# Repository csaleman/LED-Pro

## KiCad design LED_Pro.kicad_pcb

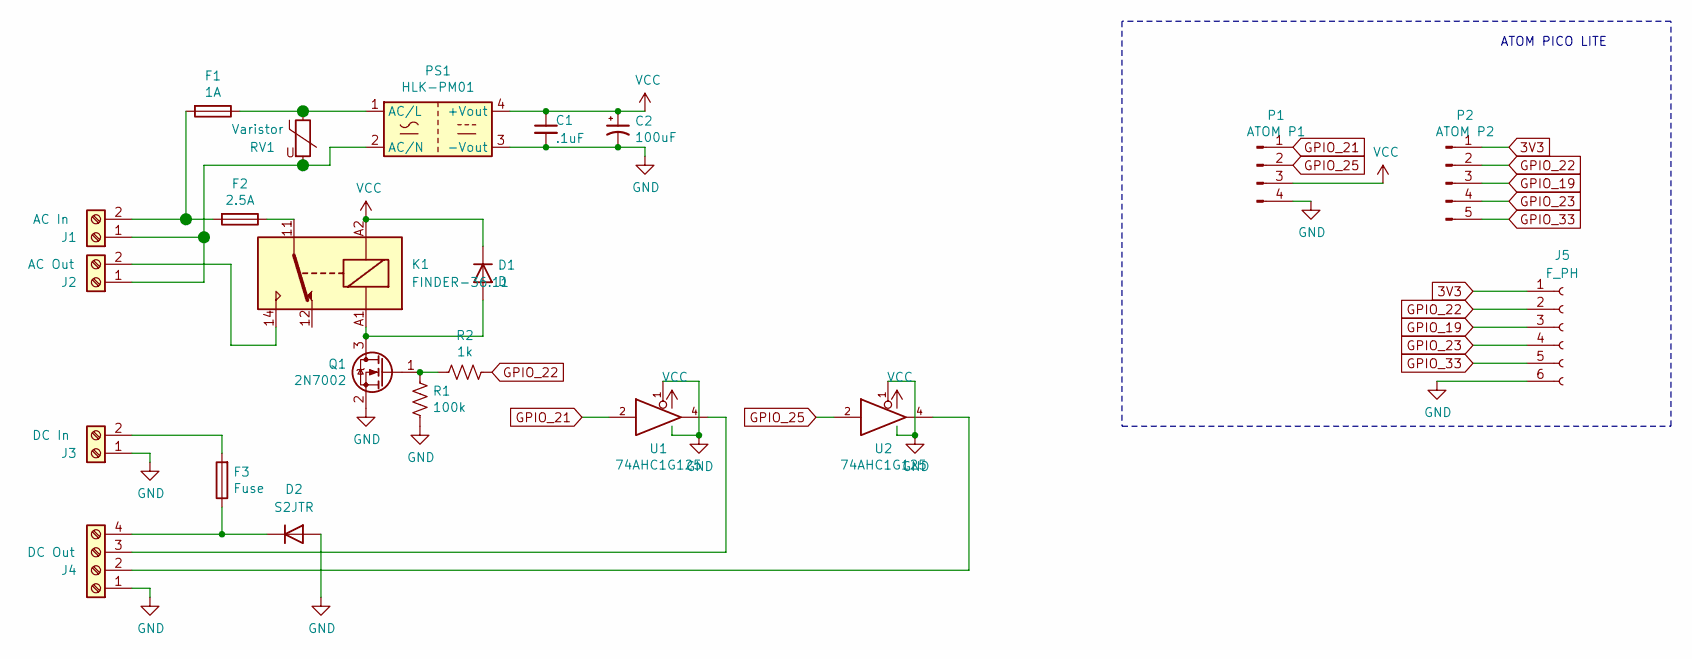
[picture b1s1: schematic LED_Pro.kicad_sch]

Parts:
C1: .1uF; C_0805_2012Metric
C2: 100uF; C_1206_3216Metric
D1: D; D_0805_2012Metric
D2: S2JTR; D_SMB
F1: 1A; RST 1-BULK
F2: 2.5A; RST 1-BULK
F3: Fuse; Fuseholder_Blade_Mini_Keystone_3568
J1: AC In; TerminalBlock_Phoenix_PT-1,5-2-5.0-H_1x02_P5.00mm_Horizontal
J2: AC Out; TerminalBlock_Phoenix_PT-1,5-2-5.0-H_1x02_P5.00mm_Horizontal
J3: DC In; TerminalBlock_Phoenix_PT-1,5-2-5.0-H_1x02_P5.00mm_Horizontal
J4: DC Out; TerminalBlock_Phoenix_PT-1,5-4-5.0-H_1x04_P5.00mm_Horizontal
J5: F_PH; PinSocket_1x06_P2.54mm_Vertical
K1: FINDER-36.11; Relay_SPDT_Finder_36.11
P1: ATOM P1; PinHeader_1x04_P2.54mm_Vertical
P2: ATOM P2; PinHeader_1x05_P2.54mm_Vertical
PS1: HLK-PM01; Converter_ACDC_HiLink_HLK-PMxx
Q1: 2N7002; SOT-23
R1: 100k; R_0805_2012Metric
R2: 1k; R_0805_2012Metric
RV1: Varistor; RV_Disc_D9mm_W3.4mm_P5mm
U1, U2: 74AHC1G125; SOT-23-5

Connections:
3V3: J5.1, P2.1
GND: C1.2, C2.2, D2.2 (A), J3.1, J4.1, J5.6, P1.4, PS1.3 (-Vout), Q1.2 (S), R1.2, U1.1, U1.3 (GND), U2.1, U2.3 (GND)
GPIO_19: J5.3, P2.3
GPIO_21: P1.1, U1.2
GPIO_22: J5.2, P2.2, R2.1
GPIO_23: J5.4, P2.4
GPIO_25: P1.2, U2.2
GPIO_33: J5.5, P2.5
unnamed: D1.2 (A), K1.A1, Q1.3 (D)
unnamed: F1.1, PS1.1 (AC/L), RV1.1
unnamed: F1.2, F2.2, J1.2
unnamed: F2.1, K1.11
unnamed: D2.1 (K), F3.1, J4.4
unnamed: F3.2, J3.2
unnamed: J1.1, J2.1, PS1.2 (AC/N), RV1.2
unnamed: J2.2, K1.14
unnamed: J4.2, U2.4
unnamed: J4.3, U1.4
unnamed: Q1.1 (G), R1.1, R2.2
VCC: C1.1, C2.1, D1.1 (K), K1.A2, P1.3, PS1.4 (+Vout), U1.5 (VCC), U2.5 (VCC)

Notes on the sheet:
ATOM PICO LITE

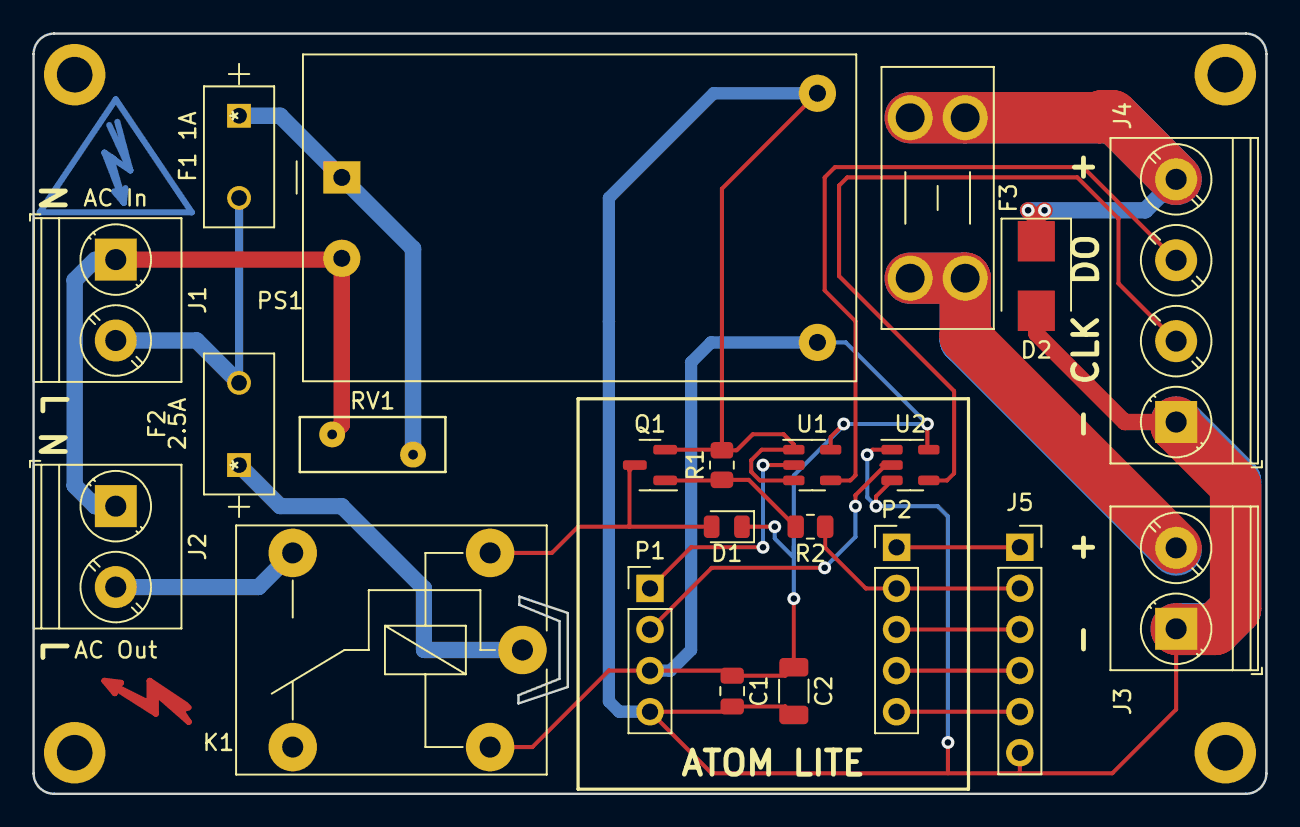
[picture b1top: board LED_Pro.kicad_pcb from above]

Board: 2 copper layers, 76.2 x 47.0 mm, 22 parts (0 on the bottom side), 20 nets.

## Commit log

2021-09-11 Added all Kicad files
2021-09-11 Added few front and back images
2023-06-04 Adding sch pdf for reference

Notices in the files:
parts and their libraries:
Copyright 2021 Accelerated Designs. All rights reserved.
